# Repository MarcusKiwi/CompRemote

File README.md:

# CompRemote

Device that lets you turn on a desktop computer using a Samsung TV remote.
Is set up to recognize the red teletext button.

This device works alongside your existing case power button, it does not replace it.
Your existing power button will still work.
The device plugs into the motherboards power button header.
Your cases power button plugs into the device instead of the motherboard.

It's powered off of a standard USB2 motherboard pin header.
On most motherboards this header will still be powered when the PC is off.
The device still needs power when the PC is off so it can listen for button presses from a remote, to turn the PC on.

# Components

Full schematics and board layout files are included in KiCad format.

* ATtiny85
* 4N25 OptoIsolator
* VS1838B Infrared Reciever
* 10k Resistor
* 1k Resistor
* Standard header strips

# Software Build Instructions

You don't have to rebuild the project, there is a precompiled CompRemote.hex you can flash with avrdude.

Download this project and [AVR-Libs](https://github.com/MarcusKiwi/AVR-Libs). Recreate this folder structure:

```
base
├───AVR-Libs
│   └───project files
└───CompRemote
    └───project files
```

Run `make` from inside the CompRemote folder to build the HEX file.

Run `make install` to build it and flash to an AVR. The default programmer type is usbasp. This can be reconfigured in the file `base/AVR-Libs/makefile`.

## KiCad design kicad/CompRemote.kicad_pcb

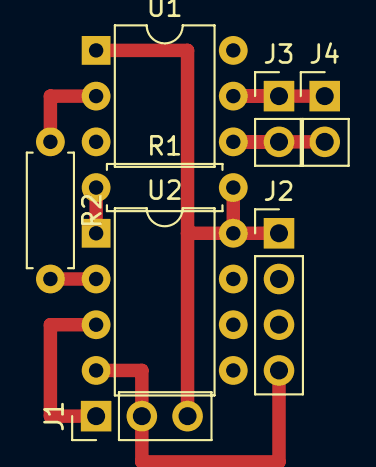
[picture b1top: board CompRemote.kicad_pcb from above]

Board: 2 copper layers, 8 parts (0 on the bottom side), 8 nets.

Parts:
J1: Conn_01x03; Pin_Header_Straight_1x03_Pitch2.54mm
J2: Conn_01x04; Pin_Header_Straight_1x04_Pitch2.54mm
J3, J4: Conn_01x02; Pin_Header_Straight_1x02_Pitch2.54mm
R1: 10K; R_Axial_DIN0207_L6.3mm_D2.5mm_P7.62mm_Horizontal
R2: 1K; R_Axial_DIN0207_L6.3mm_D2.5mm_P7.62mm_Horizontal
U1: 4N25; DIP-6_W7.62mm
U2: TINY85; DIP-8_W7.62mm

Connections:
GND: J1.2, J2.4, U2.4
IRED: J1.1, U2.3
unnamed: R1.1, U2.1
unnamed: R2.1, U1.2
OPTO: R2.2, U2.2
SIG-IN: J3.1, J4.1, U1.5
SIG-OUT: J3.2, J4.2, U1.4
VCC: J1.3, J2.1, R1.2, U1.1, U2.8

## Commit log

2016-12-29 changed paths
2018-07-28 simpler init value
2018-07-28 readme wording improvements
2018-07-28 added schematics
2018-07-28 added images
